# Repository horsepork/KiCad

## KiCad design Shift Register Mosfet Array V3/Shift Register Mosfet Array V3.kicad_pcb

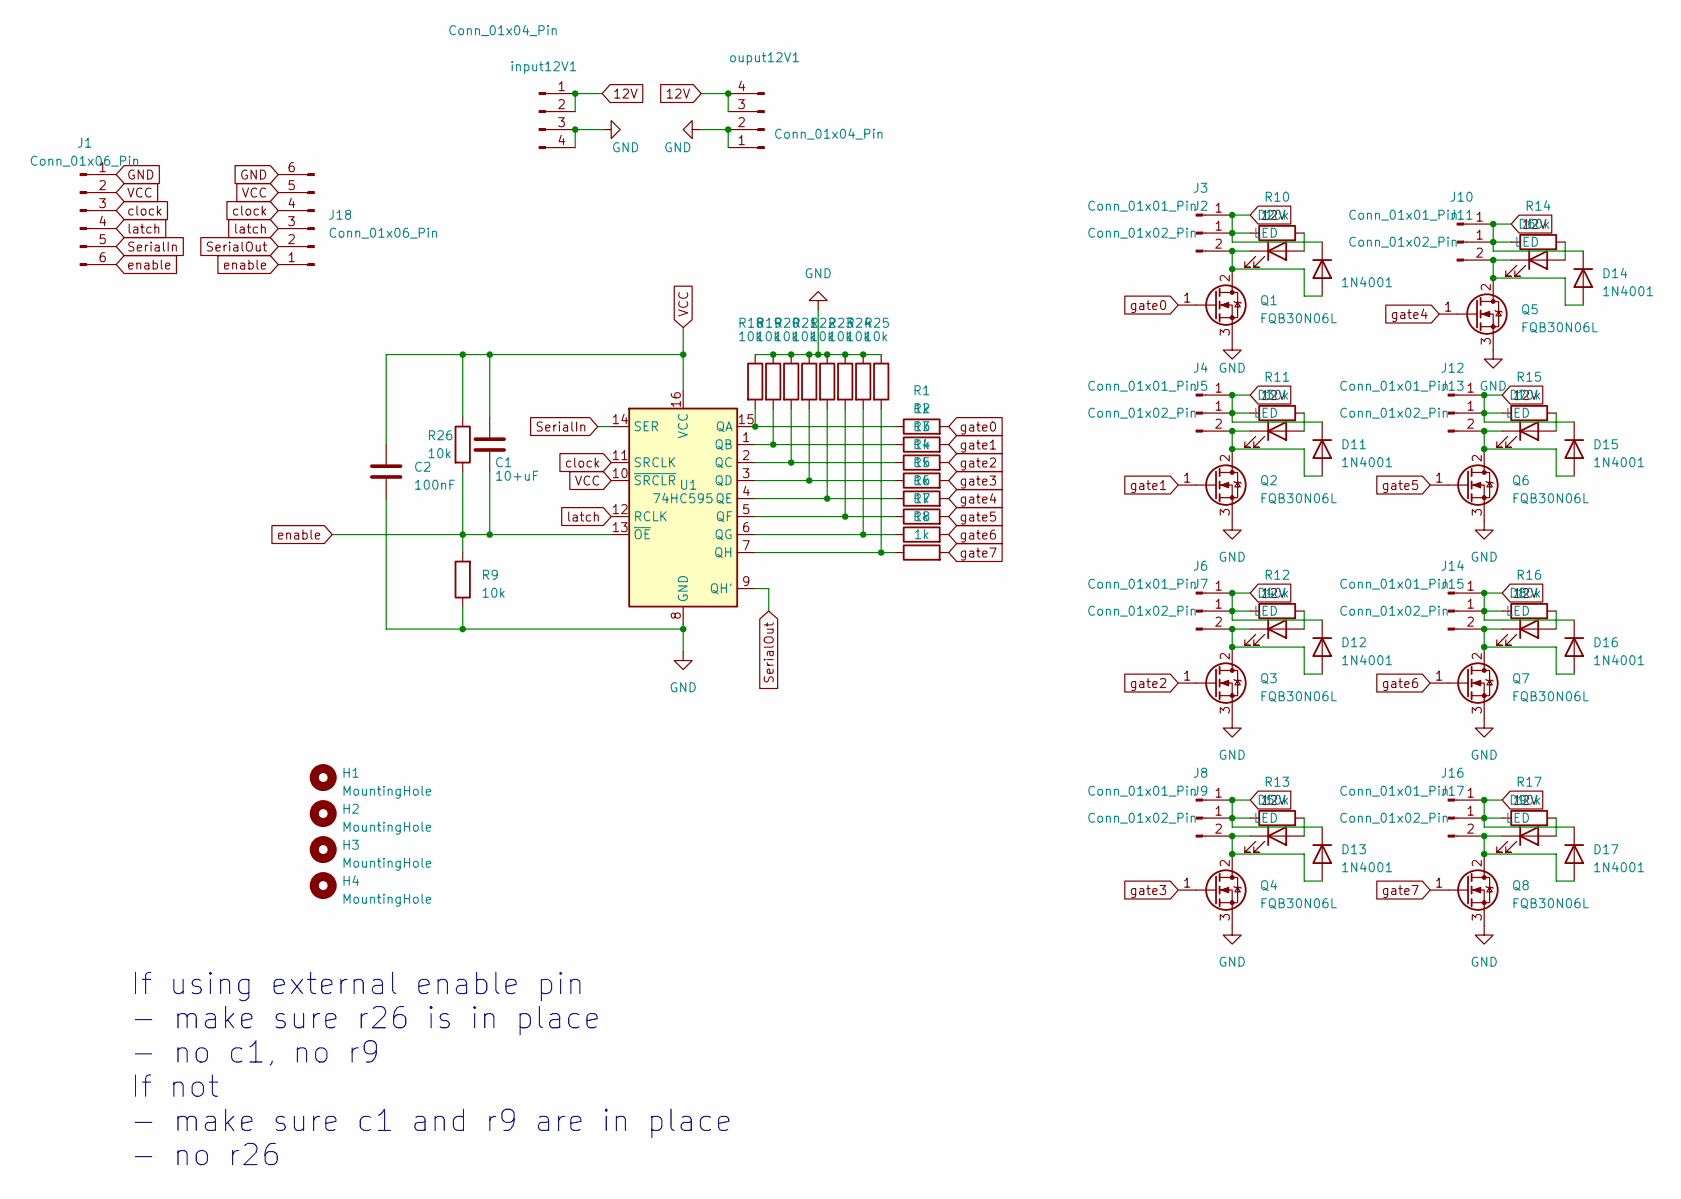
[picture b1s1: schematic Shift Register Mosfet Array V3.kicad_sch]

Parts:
C1: 10+uF; C_0805_2012Metric_Pad1.18x1.45mm_HandSolder
C2: 100nF; C_0805_2012Metric_Pad1.18x1.45mm_HandSolder
D2, D3, D4, D5, D6, D7, D8, D9: LED; LED_1206_3216Metric_Pad1.42x1.75mm_HandSolder
D10, D11, D12, D13, D14, D15, D16, D17: 1N4001; D_SMA_Handsoldering
H1, H2, H3, H4: MountingHole; MountingHole_3.2mm_M3
J1, J18: Conn_01x06_Pin; PinHeader_1x06_P2.54mm_Vertical
J2, J5, J7, J9, J11, J13, J15, J17: Conn_01x02_Pin; Molex_KK-254_AE-6410-02A_1x02_P2.54mm_Vertical
J3, J4, J6, J8, J10, J12, J14, J16: Conn_01x01_Pin; PinHeader_1x01_P2.54mm_Vertical
Q1, Q2, Q3, Q4, Q5, Q6, Q7, Q8: FQB30N06L; TO-263-2
R1, R2, R3, R4, R5, R6, R7, R8: 1k; R_0805_2012Metric_Pad1.20x1.40mm_HandSolder
R9, R10, R11, R12, R13, R14, R15, R16, R17, R18, R19, R20, R21, R22, R23, R24, R25, R26: 10k; R_0805_2012Metric_Pad1.20x1.40mm_HandSolder
U1: 74HC595; SOIC-16_3.9x9.9mm_P1.27mm
input12V1: Conn_01x04_Pin; PinHeader_1x04_P2.54mm_Vertical
ouput12V1: Conn_01x04_Pin; PinHeader_1x04_P2.54mm_Vertical

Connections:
12V: D10.1 (K), D11.1 (K), D12.1 (K), D13.1 (K), D14.1 (K), D15.1 (K), D16.1 (K), D17.1 (K), J2.1, J3.1, J4.1, J5.1, J6.1, J7.1, J8.1, J9.1, J10.1, J11.1, J12.1, J13.1, J14.1, J15.1, J16.1, J17.1, R10.1, R11.1, R12.1, R13.1, R14.1, R15.1, R16.1, R17.1, input12V1.1, input12V1.2, ouput12V1.3, ouput12V1.4
GND: C2.2, J1.1, J18.6, Q1.3 (S), Q2.3 (S), Q3.3 (S), Q4.3 (S), Q5.3 (S), Q6.3 (S), Q7.3 (S), Q8.3 (S), R9.1, R18.1, R19.1, R20.1, R21.1, R22.1, R23.1, R24.1, R25.1, U1.8 (GND), input12V1.3, input12V1.4, ouput12V1.1, ouput12V1.2
unnamed: D2.2 (A), R10.2
unnamed: D3.2 (A), R11.2
unnamed: D4.2 (A), R12.2
unnamed: D5.2 (A), R13.2
unnamed: D6.2 (A), R14.2
unnamed: D7.2 (A), R15.2
unnamed: D8.2 (A), R16.2
unnamed: D9.2 (A), R17.2
unnamed: D2.1 (K), D10.2 (A), J2.2, Q1.2 (D)
unnamed: D3.1 (K), D11.2 (A), J5.2, Q2.2 (D)
unnamed: D4.1 (K), D12.2 (A), J7.2, Q3.2 (D)
unnamed: D5.1 (K), D13.2 (A), J9.2, Q4.2 (D)
unnamed: D6.1 (K), D14.2 (A), J11.2, Q5.2 (D)
unnamed: D7.1 (K), D15.2 (A), J13.2, Q6.2 (D)
unnamed: D8.1 (K), D16.2 (A), J15.2, Q7.2 (D)
unnamed: D9.1 (K), D17.2 (A), J17.2, Q8.2 (D)
unnamed: R1.1, R18.2, U1.15 (QA)
unnamed: R2.1, R19.2, U1.1 (QB)
unnamed: R3.1, R20.2, U1.2 (QC)
unnamed: R4.1, R21.2, U1.3 (QD)
unnamed: R5.1, R22.2, U1.4 (QE)
unnamed: R6.1, R23.2, U1.5 (QF)
unnamed: R7.1, R24.2, U1.6 (QG)
unnamed: R8.1, R25.2, U1.7 (QH)
SerialIn: J1.5, U1.14 (SER)
SerialOut: J18.2, U1.9 (QH')
VCC: C1.1, C2.1, J1.2, J18.5, R26.1, U1.10 (~SRCLR), U1.16 (VCC)
clock: J1.3, J18.4, U1.11 (SRCLK)
enable: C1.2, J1.6, J18.1, R9.2, R26.2, U1.13 (~OE)
gate0: Q1.1 (G), R1.2
gate1: Q2.1 (G), R2.2
gate2: Q3.1 (G), R3.2
gate3: Q4.1 (G), R4.2
gate4: Q5.1 (G), R5.2
gate5: Q6.1 (G), R6.2
gate6: Q7.1 (G), R7.2
gate7: Q8.1 (G), R8.2
latch: J1.4, J18.3, U1.12 (RCLK)

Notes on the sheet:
If using external enable pin - make sure r26 is in place - no c1, no r9 If not - make sure c1 and r9 are in place - no r26

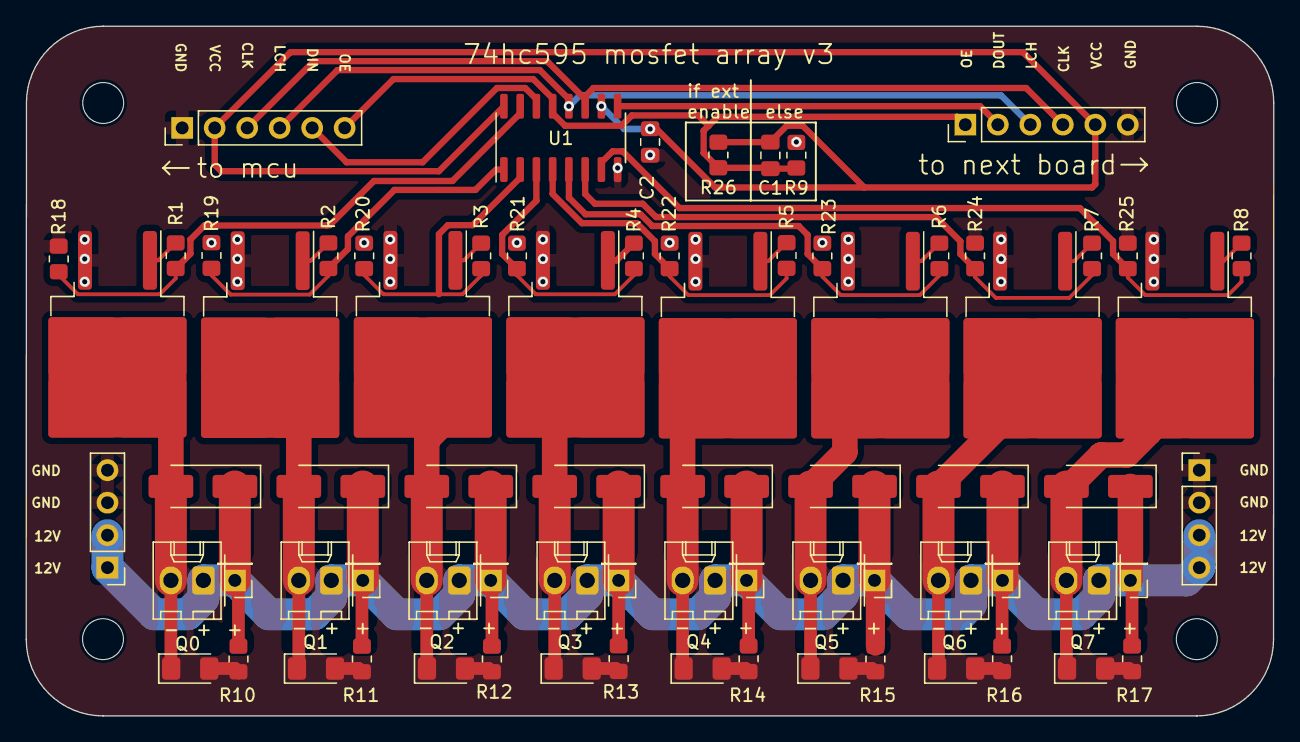
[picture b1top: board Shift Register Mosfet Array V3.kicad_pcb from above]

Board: 2 copper layers, 97.5 x 53.9 mm, 77 parts (0 on the bottom side), 40 nets.

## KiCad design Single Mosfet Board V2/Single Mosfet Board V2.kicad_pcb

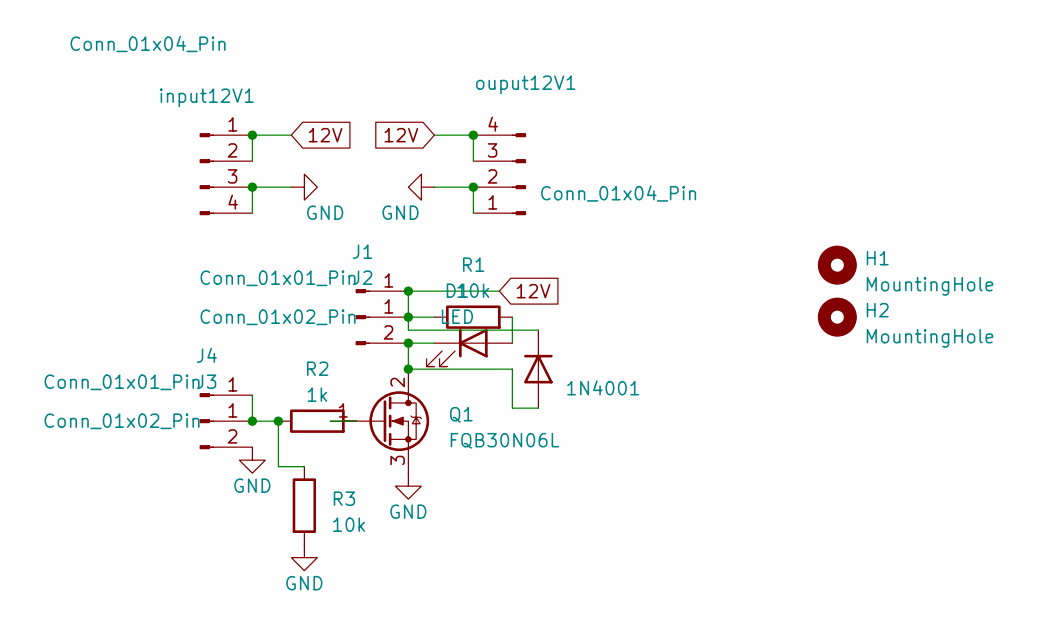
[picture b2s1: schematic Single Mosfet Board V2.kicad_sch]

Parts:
D1: LED; LED_1206_3216Metric_Pad1.42x1.75mm_HandSolder
D2: 1N4001; D_SMA_Handsoldering
H1, H2: MountingHole; MountingHole_3.2mm_M3
J1, J4: Conn_01x01_Pin; PinHeader_1x01_P2.54mm_Vertical
J2, J3: Conn_01x02_Pin; Molex_KK-254_AE-6410-02A_1x02_P2.54mm_Vertical
Q1: FQB30N06L; TO-263-2
R1, R3: 10k; R_0805_2012Metric_Pad1.20x1.40mm_HandSolder
R2: 1k; R_0805_2012Metric_Pad1.20x1.40mm_HandSolder
input12V1: Conn_01x04_Pin; PinHeader_1x04_P2.54mm_Vertical
ouput12V1: Conn_01x04_Pin; PinHeader_1x04_P2.54mm_Vertical

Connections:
12V: D2.1 (K), J1.1, J2.1, R1.1, input12V1.1, input12V1.2, ouput12V1.3, ouput12V1.4
GND: J3.2, Q1.3 (S), R3.2, input12V1.3, input12V1.4, ouput12V1.1, ouput12V1.2
unnamed: D1.2 (A), R1.2
unnamed: D1.1 (K), D2.2 (A), J2.2, Q1.2 (D)
unnamed: J3.1, J4.1, R2.1, R3.1
unnamed: Q1.1 (G), R2.2

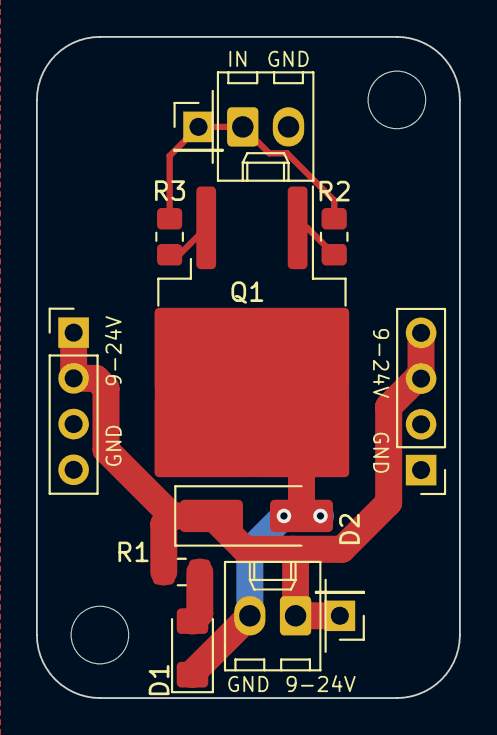
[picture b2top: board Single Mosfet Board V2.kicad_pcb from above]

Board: 2 copper layers, 23.5 x 36.7 mm, 14 parts (0 on the bottom side), 6 nets.

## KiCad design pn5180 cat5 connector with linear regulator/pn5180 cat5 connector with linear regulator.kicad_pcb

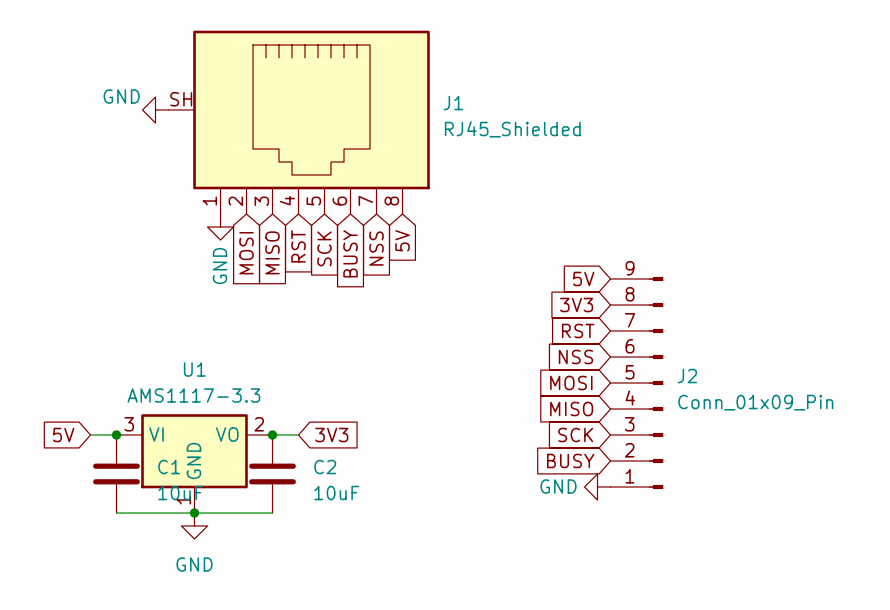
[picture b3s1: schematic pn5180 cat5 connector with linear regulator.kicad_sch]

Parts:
C1, C2: 10uF; C_Disc_D6.0mm_W2.5mm_P5.00mm
J1: RJ45_Shielded; RJ45_Ninigi_GE
J2: Conn_01x09_Pin; PinSocket_1x09_P2.54mm_Vertical
U1: AMS1117-3.3; SOT-223-3_TabPin2

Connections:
3V3: C2.1, J2.8, U1.2 (VO)
5V: C1.1, J1.8, J2.9, U1.3 (VI)
BUSY: J1.6, J2.2
GND: C1.2, C2.2, J1.1, J1.SH, J2.1, U1.1 (GND)
MISO: J1.3, J2.4
MOSI: J1.2, J2.5
NSS: J1.7, J2.6
RST: J1.4, J2.7
SCK: J1.5, J2.3

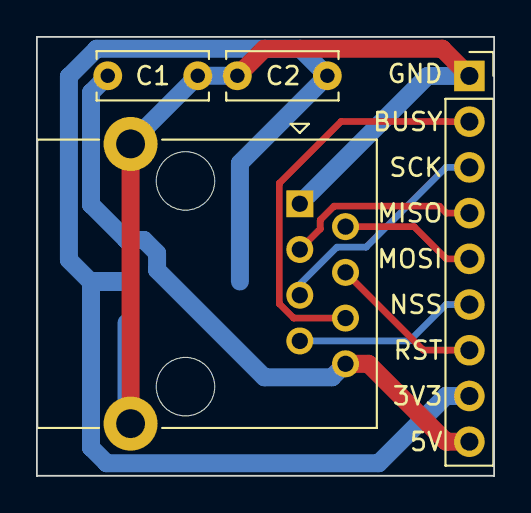
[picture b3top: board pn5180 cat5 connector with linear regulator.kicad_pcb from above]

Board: 2 copper layers, 25.4 x 24.4 mm, 5 parts (1 on the bottom side), 9 nets.

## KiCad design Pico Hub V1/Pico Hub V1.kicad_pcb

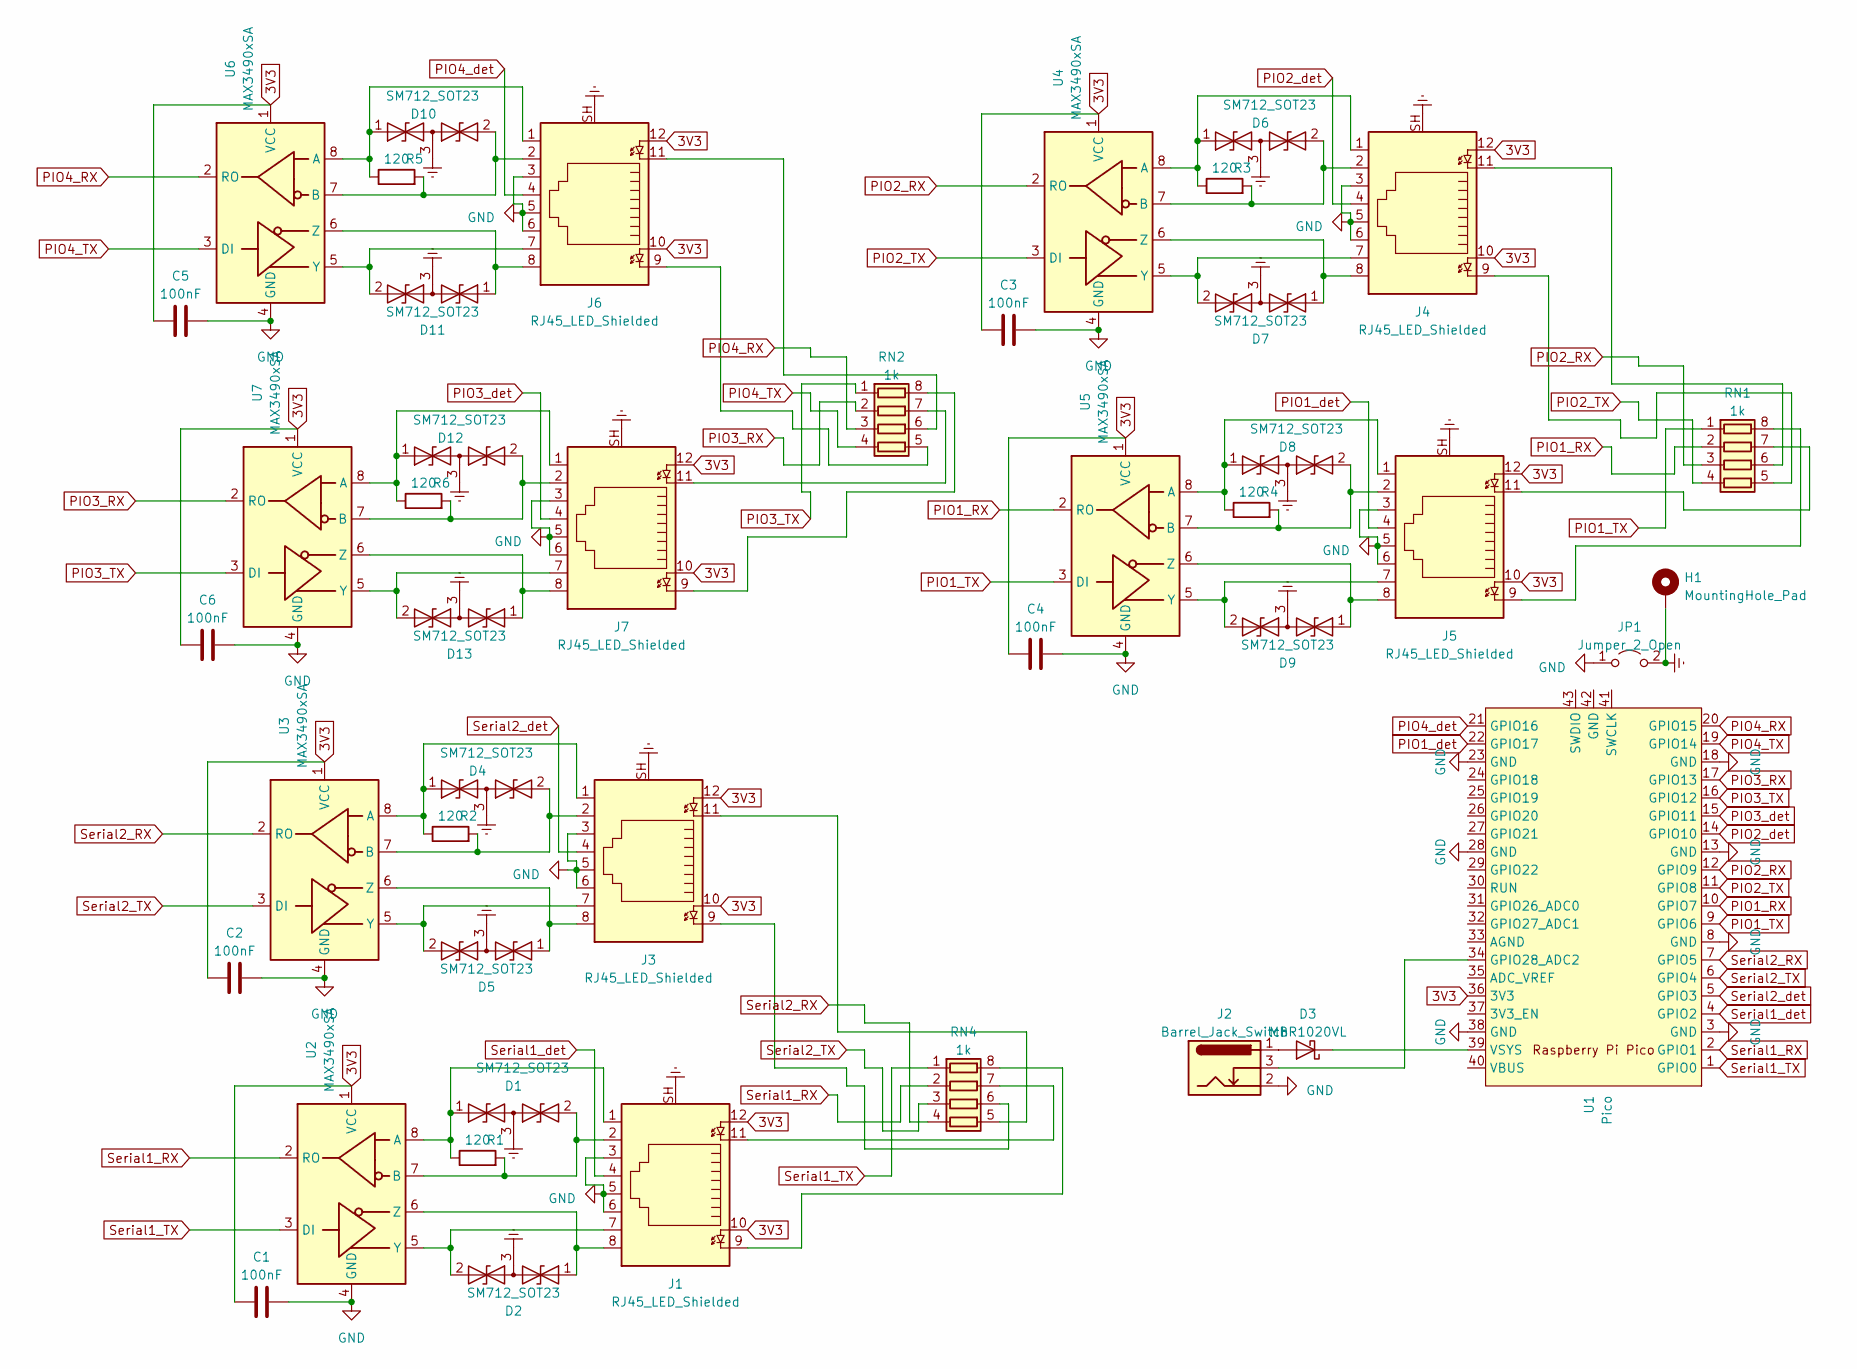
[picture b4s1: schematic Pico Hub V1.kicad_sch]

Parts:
C1, C2, C3, C4, C5, C6: 100nF; C_0805_2012Metric_Pad1.18x1.45mm_HandSolder
D1, D2, D4, D5, D6, D7, D8, D9, D10, D11, D12, D13: SM712_SOT23; SOT-23
D3: MBR1020VL; D_SOD-123F
H1: MountingHole_Pad; MountingHole_3.7mm_Pad_Via
J1, J3, J4, J5, J6, J7: RJ45_LED_Shielded; RJ45_Amphenol_RJHSE538X
J2: Barrel_Jack_Switch; BarrelJack_GCT_DCJ200-10-A_Horizontal
JP1: Jumper_2_Open; SolderJumper-2_P1.3mm_Open_RoundedPad1.0x1.5mm
R1, R2, R3, R4, R5, R6: 120; R_0805_2012Metric_Pad1.20x1.40mm_HandSolder
RN1, RN2, RN4: 1k; R_Array_Convex_4x0603
U1: Pico; RPi_Pico_SMD_TH_No_Pads
U2, U3, U4, U5, U6, U7: MAX3490xSA; SOIC-8_3.9x4.9mm_P1.27mm

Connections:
3V3: C1.2, C2.2, C3.2, C4.2, C5.2, C6.2, J1.10, J1.12, J3.10, J3.12, J4.10, J4.12, J5.10, J5.12, J6.10, J6.12, J7.10, J7.12, U1.36 (3V3), U2.1 (VCC), U3.1 (VCC), U4.1 (VCC), U5.1 (VCC), U6.1 (VCC), U7.1 (VCC)
Earth: D1.3 (common), D2.3 (common), D4.3 (common), D5.3 (common), D6.3 (common), D7.3 (common), D8.3 (common), D9.3 (common), D10.3 (common), D11.3 (common), D12.3 (common), D13.3 (common), H1.1, J1.SH, J3.SH, J4.SH, J5.SH, J6.SH, J7.SH, JP1.2 (B)
GND: C1.1, C2.1, C3.1, C4.1, C5.1, C6.1, J1.3, J1.5, J1.6, J2.2, J3.3, J3.5, J3.6, J4.3, J4.5, J4.6, J5.3, J5.5, J5.6, J6.3, J6.5, J6.6, J7.3, J7.5, J7.6, JP1.1 (A), U1.3 (GND), U1.8 (GND), U1.13 (GND), U1.18 (GND), U1.23 (GND), U1.28 (GND), U1.38 (GND), U2.4 (GND), U3.4 (GND), U4.4 (GND), U5.4 (GND), U6.4 (GND), U7.4 (GND)
unnamed: D1.1 (A1), J1.1, R1.1, U2.8 (A)
unnamed: D1.2 (A2), J1.2, R1.2, U2.7 (B)
unnamed: D2.1 (A1), J1.8, U2.6 (Z)
unnamed: D2.2 (A2), J1.7, U2.5 (Y)
unnamed: D3.2 (A), J2.1
unnamed: D3.1 (K), U1.39 (VSYS)
unnamed: D4.1 (A1), J3.1, R2.1, U3.8 (A)
unnamed: D4.2 (A2), J3.2, R2.2, U3.7 (B)
unnamed: D5.1 (A1), J3.8, U3.6 (Z)
unnamed: D5.2 (A2), J3.7, U3.5 (Y)
unnamed: D6.1 (A1), J4.1, R3.1, U4.8 (A)
unnamed: D6.2 (A2), J4.2, R3.2, U4.7 (B)
unnamed: D7.1 (A1), J4.8, U4.6 (Z)
unnamed: D7.2 (A2), J4.7, U4.5 (Y)
unnamed: D8.1 (A1), J5.1, R4.1, U5.8 (A)
unnamed: D8.2 (A2), J5.2, R4.2, U5.7 (B)
unnamed: D9.1 (A1), J5.8, U5.6 (Z)
unnamed: D9.2 (A2), J5.7, U5.5 (Y)
unnamed: D10.1 (A1), J6.1, R5.1, U6.8 (A)
unnamed: D10.2 (A2), J6.2, R5.2, U6.7 (B)
unnamed: D11.1 (A1), J6.8, U6.6 (Z)
unnamed: D11.2 (A2), J6.7, U6.5 (Y)
unnamed: D12.1 (A1), J7.1, R6.1, U7.8 (A)
unnamed: D12.2 (A2), J7.2, R6.2, U7.7 (B)
unnamed: D13.1 (A1), J7.8, U7.6 (Z)
unnamed: D13.2 (A2), J7.7, U7.5 (Y)
unnamed: J5.9, RN1.8 (R1.2)
unnamed: J5.11, RN1.7 (R2.2)
unnamed: J4.11, RN1.6 (R3.2)
unnamed: J4.9, RN1.5 (R4.2)
unnamed: J7.9, RN2.8 (R1.2)
unnamed: J7.11, RN2.7 (R2.2)
unnamed: J6.11, RN2.6 (R3.2)
unnamed: J6.9, RN2.5 (R4.2)
unnamed: J1.9, RN4.8 (R1.2)
unnamed: J1.11, RN4.7 (R2.2)
unnamed: J3.9, RN4.6 (R3.2)
unnamed: J3.11, RN4.5 (R4.2)
unnamed: J2.3, U1.34 (GPIO28_ADC2)
PIO1_RX: RN1.2 (R2.1), U1.10 (GPIO7), U5.2 (RO)
PIO1_TX: RN1.1 (R1.1), U1.9 (GPIO6), U5.3 (DI)
PIO1_det: J5.4, U1.22 (GPIO17)
PIO2_RX: RN1.3 (R3.1), U1.12 (GPIO9), U4.2 (RO)
PIO2_TX: RN1.4 (R4.1), U1.11 (GPIO8), U4.3 (DI)
PIO2_det: J4.4, U1.14 (GPIO10)
PIO3_RX: RN2.2 (R2.1), U1.17 (GPIO13), U7.2 (RO)
PIO3_TX: RN2.1 (R1.1), U1.16 (GPIO12), U7.3 (DI)
PIO3_det: J7.4, U1.15 (GPIO11)
PIO4_RX: RN2.3 (R3.1), U1.20 (GPIO15), U6.2 (RO)
PIO4_TX: RN2.4 (R4.1), U1.19 (GPIO14), U6.3 (DI)
PIO4_det: J6.4, U1.21 (GPIO16)
Serial1_RX: RN4.2 (R2.1), U1.2 (GPIO1), U2.2 (RO)
Serial1_TX: RN4.1 (R1.1), U1.1 (GPIO0), U2.3 (DI)
Serial1_det: J1.4, U1.4 (GPIO2)
Serial2_RX: RN4.4 (R4.1), U1.7 (GPIO5), U3.2 (RO)
Serial2_TX: RN4.3 (R3.1), U1.6 (GPIO4), U3.3 (DI)
Serial2_det: J3.4, U1.5 (GPIO3)

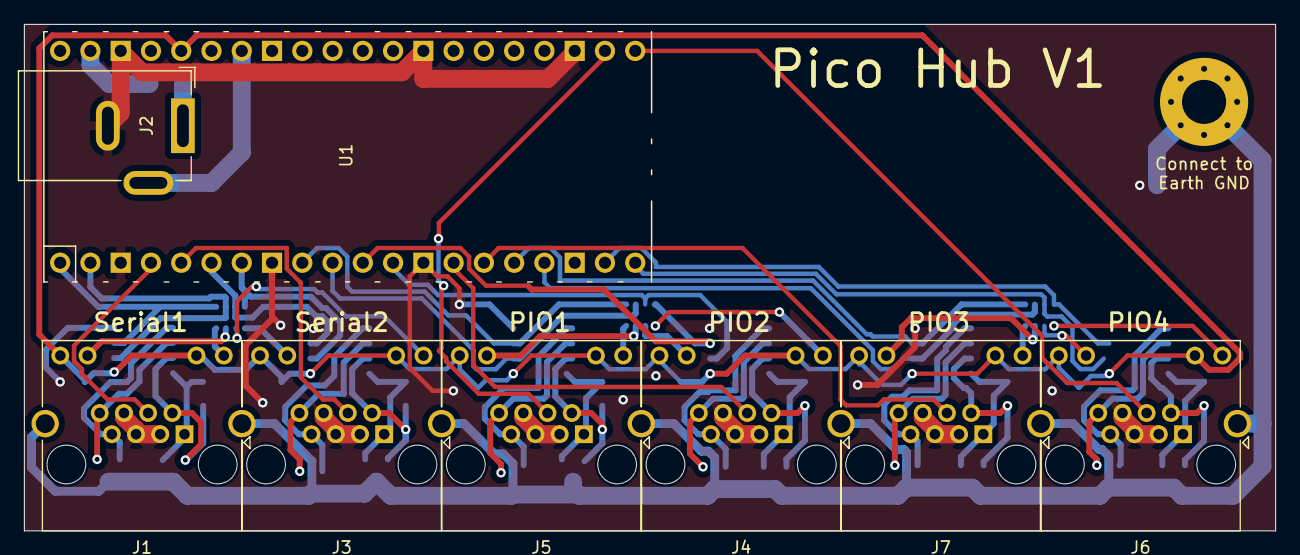
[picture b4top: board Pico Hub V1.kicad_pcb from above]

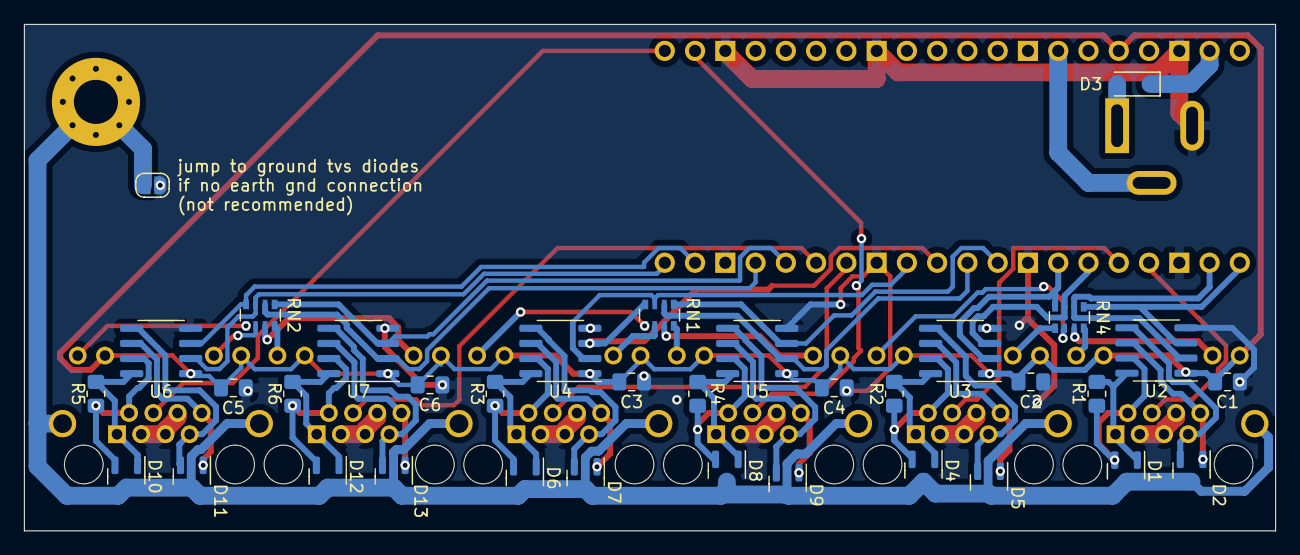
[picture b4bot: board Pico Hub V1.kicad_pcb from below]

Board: 2 copper layers, 105.0 x 42.5 mm, 44 parts (35 on the bottom side), 60 nets.

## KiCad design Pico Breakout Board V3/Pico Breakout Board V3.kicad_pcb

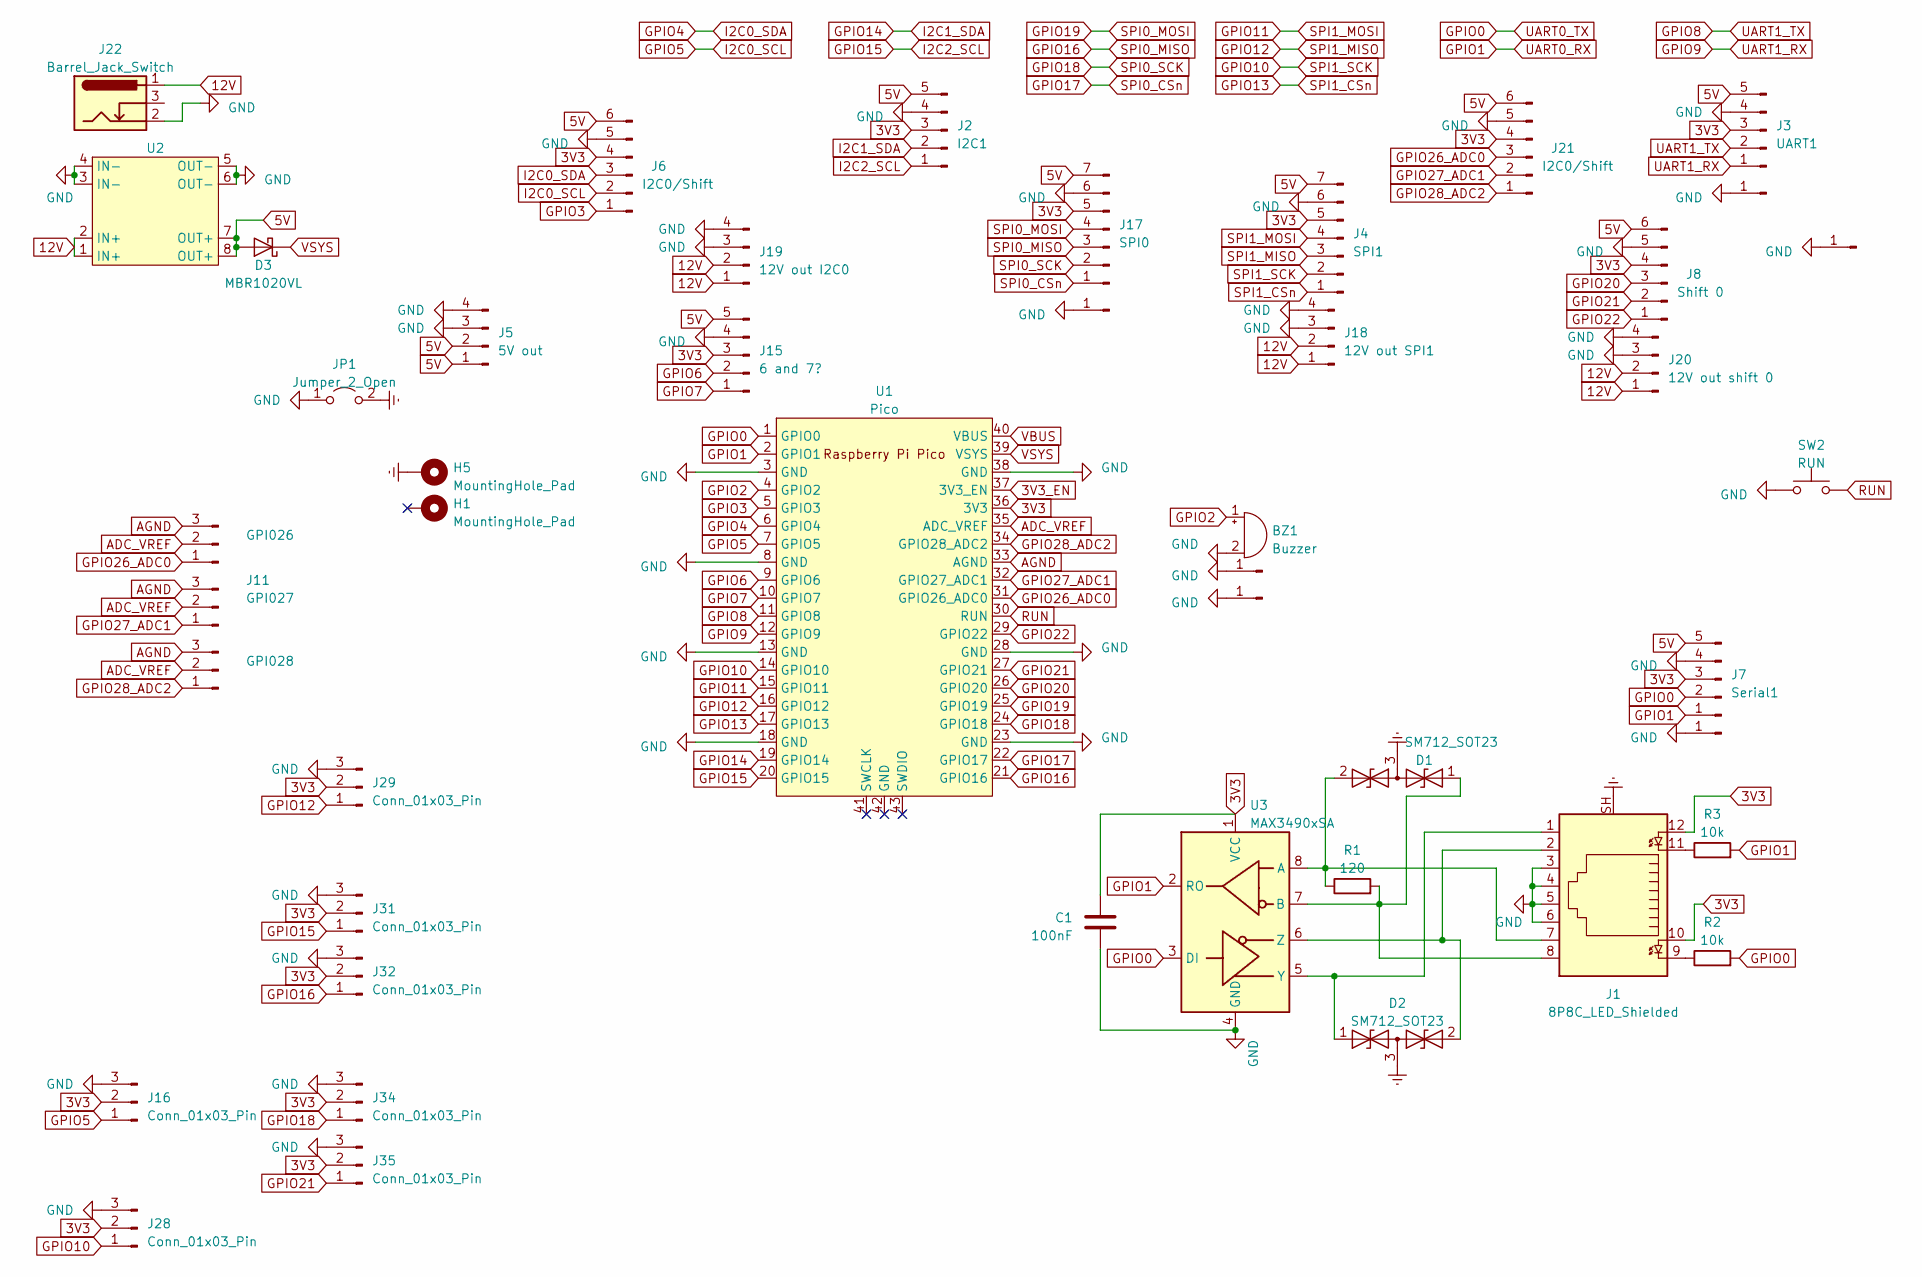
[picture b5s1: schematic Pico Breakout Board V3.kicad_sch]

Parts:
BZ1: Buzzer; Buzzer_12x9.5RM7.6
C1: 100nF; C_0805_2012Metric_Pad1.18x1.45mm_HandSolder
D1, D2: SM712_SOT23; SOT-23
D3: MBR1020VL; D_SOD-123F
H1, H5: MountingHole_Pad; MountingHole_3.7mm_Pad_Via
J1: 8P8C_LED_Shielded; RJ45_Amphenol_RJHSE538X
J2: I2C1; Molex_KK-254_AE-6410-05A_1x05_P2.54mm_Vertical
J3: UART1; Molex_KK-254_AE-6410-05A_1x05_P2.54mm_Vertical
J4: SPI1; Molex_KK-254_AE-6410-07A_1x07_P2.54mm_Vertical
J5: 5V out; Molex_KK-254_AE-6410-04A_1x04_P2.54mm_Vertical
J6, J21: I2C0/Shift; Molex_KK-254_AE-6410-06A_1x06_P2.54mm_Vertical
J7: Serial1; Molex_KK-254_AE-6410-05A_1x05_P2.54mm_Vertical
J8: Shift 0; Molex_KK-254_AE-6410-06A_1x06_P2.54mm_Vertical
J9: GPI026; Molex_KK-254_AE-6410-03A_1x03_P2.54mm_Vertical
J10, J12, J14, J23, J24, J25: Conn_01x01_Pin; PinHeader_1x01_P2.54mm_Vertical
J11: GPI027; Molex_KK-254_AE-6410-03A_1x03_P2.54mm_Vertical
J13: GPI028; Molex_KK-254_AE-6410-03A_1x03_P2.54mm_Vertical
J15: 6 and 7?; Molex_KK-254_AE-6410-05A_1x05_P2.54mm_Vertical
J16, J28, J29, J31, J32, J34, J35: Conn_01x03_Pin; Molex_KK-254_AE-6410-03A_1x03_P2.54mm_Vertical
J17: SPI0; Molex_KK-254_AE-6410-07A_1x07_P2.54mm_Vertical
J18: 12V out SPI1; Molex_KK-254_AE-6410-04A_1x04_P2.54mm_Vertical
J19: 12V out I2C0; Molex_KK-254_AE-6410-04A_1x04_P2.54mm_Vertical
J20: 12V out shift 0; Molex_KK-254_AE-6410-04A_1x04_P2.54mm_Vertical
J22: Barrel_Jack_Switch; BarrelJack_GCT_DCJ200-10-A_Horizontal
JP1: Jumper_2_Open; SolderJumper-2_P1.3mm_Open_RoundedPad1.0x1.5mm
R1: 120; R_0805_2012Metric_Pad1.20x1.40mm_HandSolder
R2, R3: 10k; R_0805_2012Metric_Pad1.20x1.40mm_HandSolder
SW2: RUN; SW_PUSH_6mm
U1: Pico; RPi_Pico_SMD_TH_No_Pads_No_Debug_No_USB
U2: Mini MP1584EN
U3: MAX3490xSA; SOIC-8_3.9x4.9mm_P1.27mm

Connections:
3V3: C1.1, J1.10, J1.12, J2.3, J3.3, J4.5, J6.4, J7.3, J8.4, J15.3, J16.2, J17.5, J21.4, J28.2, J29.2, J31.2, J32.2, J34.2, J35.2, U1.36 (3V3), U3.1 (VCC)
3V3_EN: U1.37 (3V3_EN)
5V: D3.2 (A), J2.5, J3.5, J4.7, J5.1, J5.2, J6.6, J7.5, J8.6, J15.5, J17.7, J21.6, U2.7 (OUT+), U2.8 (OUT+)
12V: J18.1, J18.2, J19.1, J19.2, J20.1, J20.2, J22.1, U2.1 (IN+), U2.2 (IN+)
ADC_VREF: J9.2, J11.2, J13.2, U1.35 (ADC_VREF)
AGND: J9.3, J11.3, J13.3, U1.33 (AGND)
Earth: D1.3 (common), D2.3 (common), H5.1, J1.SH, JP1.2 (B)
GND: BZ1.2 (+), C1.2, J1.3, J1.4, J1.5, J1.6, J2.4, J3.4, J4.6, J5.3, J5.4, J6.5, J7.4, J8.5, J10.1, J12.1, J14.1, J15.4, J16.3, J17.6, J18.3, J18.4, J19.3, J19.4, J20.3, J20.4, J21.5, J22.2, J23.1, J24.1, J25.1, J28.3, J29.3, J31.3, J32.3, J34.3, J35.3, JP1.1 (A), SW2.1, U1.3 (GND), U1.8 (GND), U1.13 (GND), U1.18 (GND), U1.23 (GND), U1.28 (GND), U1.38 (GND), U2.3 (IN-), U2.4 (IN-), U2.5 (OUT-), U2.6 (OUT-), U3.4 (GND)
GPIO0: J7.2, R2.2, U1.1 (GPIO0), U3.3 (DI)
GPIO1: J7.1, R3.2, U1.2 (GPIO1), U3.2 (RO)
GPIO2: BZ1.1 (-), U1.4 (GPIO2)
GPIO3: J6.1, U1.5 (GPIO3)
GPIO4: J6.3, U1.6 (GPIO4)
GPIO5: J6.2, J16.1, U1.7 (GPIO5)
GPIO6: J15.2, U1.9 (GPIO6)
GPIO7: J15.1, U1.10 (GPIO7)
GPIO8: J3.2, U1.11 (GPIO8)
GPIO9: J3.1, U1.12 (GPIO9)
GPIO10: J4.2, J28.1, U1.14 (GPIO10)
GPIO11: J4.4, U1.15 (GPIO11)
GPIO12: J4.3, J29.1, U1.16 (GPIO12)
GPIO13: J4.1, U1.17 (GPIO13)
GPIO14: J2.2, U1.19 (GPIO14)
GPIO15: J2.1, J31.1, U1.20 (GPIO15)
GPIO16: J17.3, J32.1, U1.21 (GPIO16)
GPIO17: J17.1, U1.22 (GPIO17)
GPIO18: J17.2, J34.1, U1.24 (GPIO18)
GPIO19: J17.4, U1.25 (GPIO19)
GPIO20: J8.3, U1.26 (GPIO20)
GPIO21: J8.2, J35.1, U1.27 (GPIO21)
GPIO22: J8.1, U1.29 (GPIO22)
GPIO26_ADC0: J9.1, J21.3, U1.31 (GPIO26_ADC0)
GPIO27_ADC1: J11.1, J21.2, U1.32 (GPIO27_ADC1)
GPIO28_ADC2: J13.1, J21.1, U1.34 (GPIO28_ADC2)
unnamed: D1.1 (A1), J1.8, R1.2, U3.7 (B)
unnamed: D1.2 (A2), J1.7, R1.1, U3.8 (A)
unnamed: D2.1 (A1), J1.1, U3.5 (Y)
unnamed: D2.2 (A2), J1.2, U3.6 (Z)
unnamed: J1.9, R2.1
unnamed: J1.11, R3.1
RUN: SW2.2, U1.30 (RUN)
VBUS: U1.40 (VBUS)
VSYS: D3.1 (K), U1.39 (VSYS)

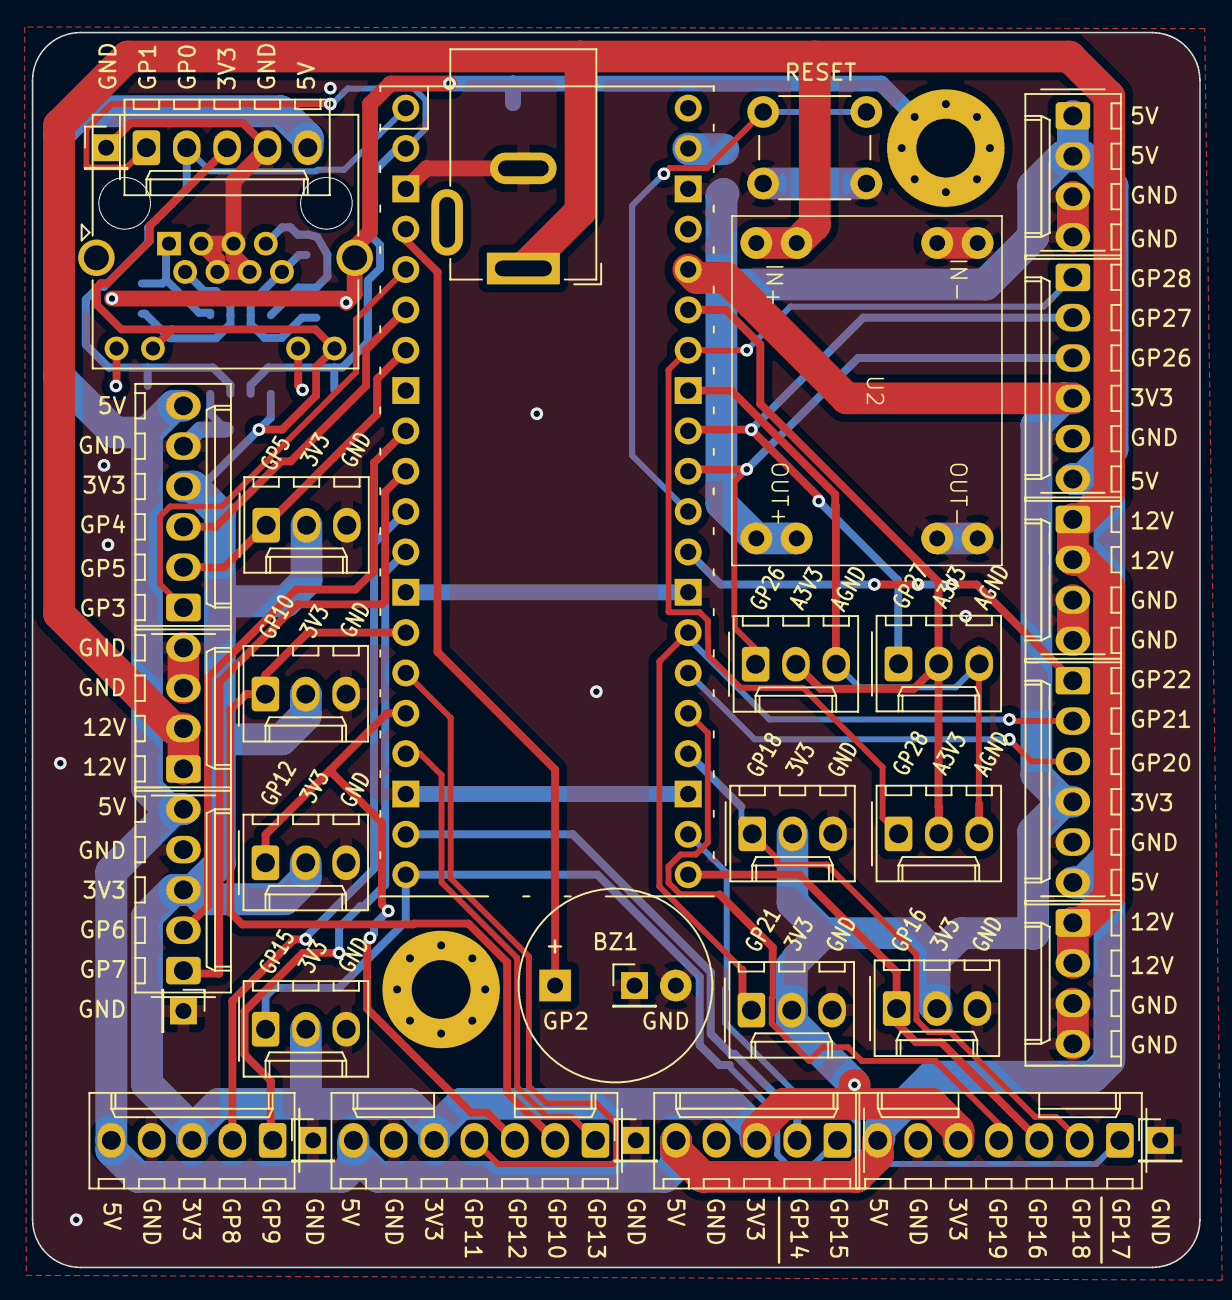
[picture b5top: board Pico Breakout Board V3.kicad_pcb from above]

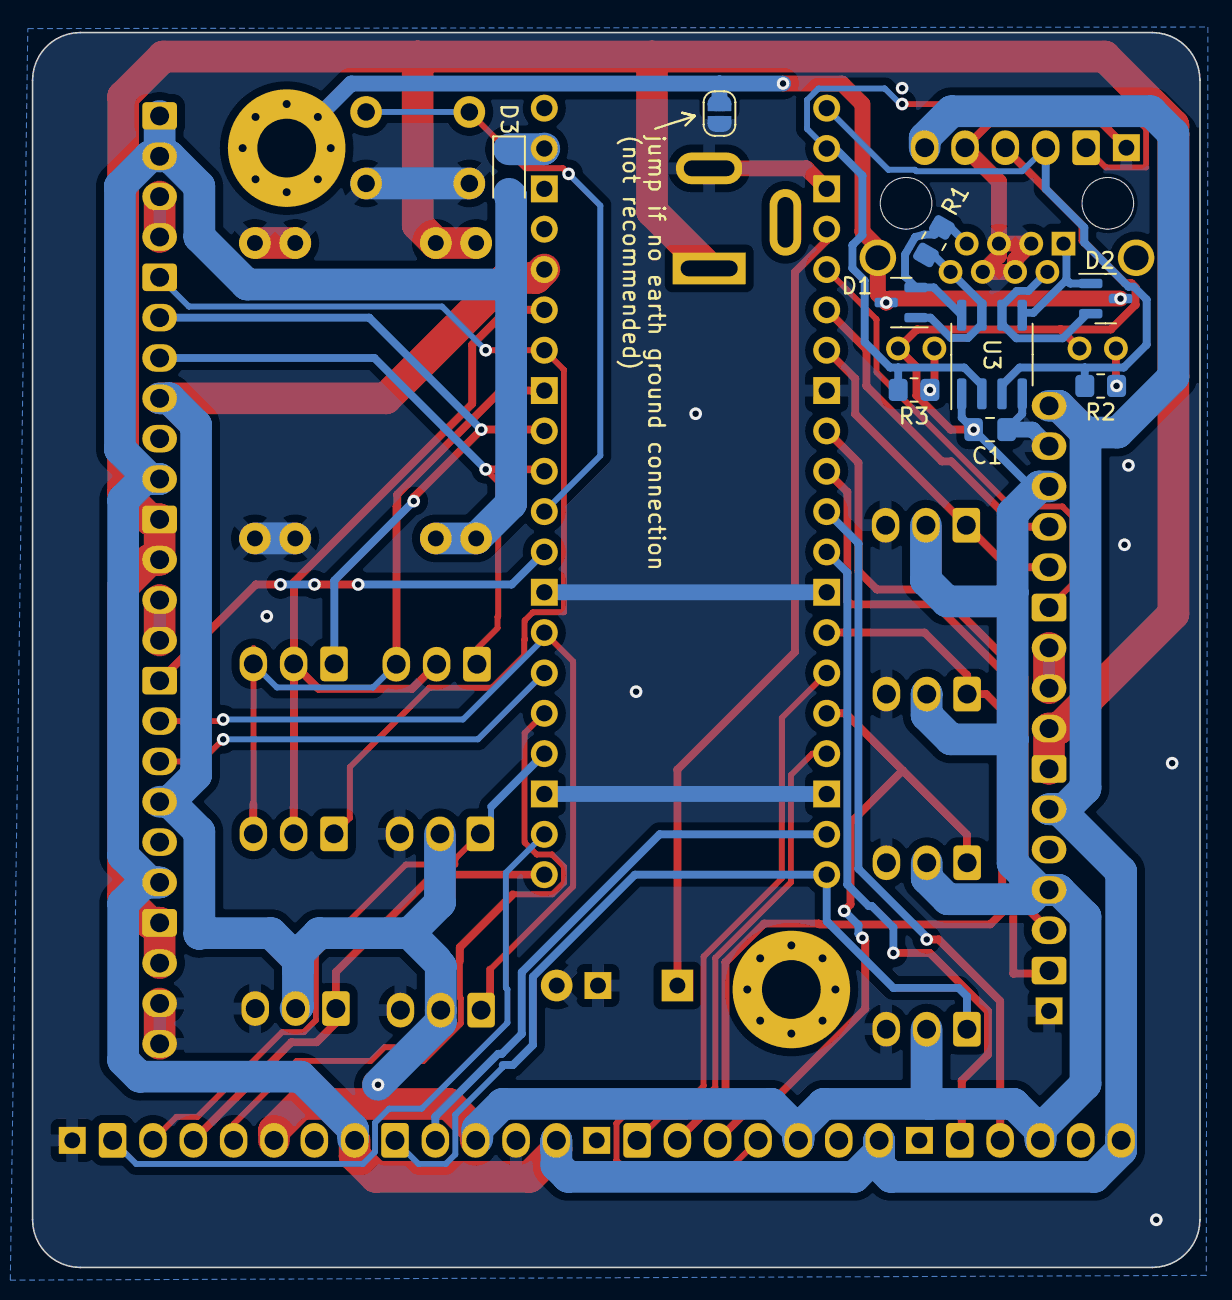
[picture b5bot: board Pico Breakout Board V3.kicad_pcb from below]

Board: 2 copper layers, 73.5 x 77.8 mm, 46 parts (9 on the bottom side), 41 nets.
